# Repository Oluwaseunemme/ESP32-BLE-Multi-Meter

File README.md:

# ⚡ ESP32 BLE Multi-Meter

A custom **ESP32-based digital multimeter** capable of measuring **DC voltage, resistance, continuity, diode forward voltage, and capacitance**, with measurement results transmitted wirelessly to a **Flutter mobile application over Bluetooth Low Energy (BLE)**.

The project combines embedded firmware, analog measurement circuits, OLED display control, BLE communication, Flutter application development, KiCad PCB design, Proteus simulation, and object-oriented C++ firmware architecture.

---

## 📌 Project Overview

This project started as a collection of individual measurement experiments and evolved into a single multifunctional ESP32-based meter.

The meter can:

* Measure DC voltage
* Measure resistance
* Perform continuity testing
* Measure diode forward voltage
* Measure capacitance
* Display measurements locally on a **128×64 OLED**
* Send measurement results to a Flutter mobile application through **BLE**
* Provide a built-in resistor color-code calculator
* Calculate resistor series and parallel combinations
* Calculate capacitor series and parallel combinations
* Switch between measurement modes from the mobile application

The repository also contains the development stages of the project, including individual measurement programs, simulations, circuit designs, PCB layouts, and the final object-oriented firmware.

---

# 🧩 System Architecture

```text
                    ┌──────────────────────┐
                    │      Test Leads      │
                    └──────────┬───────────┘
                               │
                               ▼
                    ┌──────────────────────┐
                    │ Measurement Circuits │
                    │                      │
                    │ • Voltage            │
                    │ • Resistance          │
                    │ • Continuity         │
                    │ • Diode              │
                    │ • Capacitance        │
                    └──────────┬───────────┘
                               │
                               ▼
                    ┌──────────────────────┐
                    │        ESP32         │
                    │                      │
                    │ • ADC measurement    │
                    │ • Mode control       │
                    │ • Calculations       │
                    │ • OLED interface     │
                    │ • BLE communication  │
                    └───────┬───────┬──────┘
                            │       │
                     ┌──────▼───┐   │
                     │  OLED    │   │ BLE
                     │ 128×64   │   │
                     └──────────┘   │
                                    ▼
                          ┌──────────────────┐
                          │ Flutter Mobile   │
                          │      App         │
                          │                  │
                          │ • Live readings  │
                          │ • Calculators    │
                          │ • BLE interface  │
                          └──────────────────┘
```

---

# 🔧 Measurement Functions

## 1. Voltage Measurement

The ESP32 ADC is used to measure the scaled input voltage.

A resistor-divider network reduces the measured voltage to a level suitable for the ESP32 ADC, after which the firmware reconstructs the original voltage.

```text
Input Voltage
      │
      ▼
Resistor Divider
      │
      ▼
    ESP32 ADC
      │
      ▼
Voltage Calculation
      │
      ▼
OLED / BLE / Flutter
```

---

## 2. Resistance Measurement

Resistance is determined using a known reference resistor and the voltage developed across the unknown resistor.

Using the voltage-divider relationship:

$$
R_x = \frac{R_{ref}V_x}{V_{in}-V_x}
$$

The firmware converts the ADC measurement into resistance and automatically formats the result into an appropriate unit.

Example:

```text
35.30 Ω
497.47 Ω
12.00 kΩ
```

---

## 3. Continuity Testing

The continuity mode checks whether the resistance between the probes is below a defined threshold.

When continuity is detected, the meter can provide an audible indication through a buzzer while also displaying the result locally.

This makes the resistance measurement hardware usable as a dedicated continuity tester.

---

## 4. Diode Testing

The diode mode applies a controlled test condition to the diode and measures its forward voltage.

The measured voltage is then displayed as the diode's approximate forward voltage:

```text
Forward Voltage
      │
      ▼
   ESP32 ADC
      │
      ▼
Voltage Conversion
      │
      ▼
 OLED / Flutter
```

---

# 5. Capacitance Measurement

Capacitance is measured using the **RC charging time** of the capacitor under test.

For an RC circuit:

$$
V_C(t)=V_{CC}(1-e^{-t/RC})
$$

At approximately **63.2%** of the charging voltage:

$$
t=RC
$$

Therefore:

$$
\boxed{C=\frac{t}{R}}
$$

The firmware measures how long the capacitor takes to reach the 63.2% threshold and calculates its capacitance.

### Automatic Range Selection

Multiple charging resistors are used to accommodate different capacitor values.

```text
1 MΩ
100 kΩ
10 kΩ
1 kΩ
```

The firmware can select an appropriate resistor depending on the charging time, preventing large capacitors from requiring unnecessarily long measurements.

A transistor-controlled discharge path is also used to reset the capacitor before another measurement.

---

# 📱 Flutter BLE Application

The meter communicates with the mobile application using **Bluetooth Low Energy**.

The Flutter application provides:

### Live Measurement

Measurement values received from the ESP32 can be displayed on the phone.

```text
ESP32
  │
  │ BLE
  ▼
Flutter BLE Manager
  │
  ▼
Mobile UI
```

This allows the meter to function as both a standalone instrument and a wireless measurement device.

### Built-in Calculator

The application also contains several electronics calculators.

#### Resistor Color Code

The user can select resistor color bands and calculate the corresponding resistance and tolerance.

#### Resistor Series / Parallel

The application calculates equivalent resistance for:

* Series connections
* Parallel connections

#### Capacitor Series / Parallel

Equivalent capacitance can also be calculated for series and parallel capacitor configurations.

This makes the application useful not only for displaying measurements but also as a small electronics utility tool.

---

# 🖥️ Local OLED Interface

The meter uses a **128×64 OLED display** for local operation.

The OLED provides:

* Measurement values
* Measurement mode
* Meter status
* Local user feedback

The OLED allows the ESP32 meter to remain fully functional even when the phone is not connected.

---

# 🧠 Firmware Architecture

The project was developed progressively.

Individual measurement modes were first implemented and tested separately before being combined into the final meter firmware.

The repository therefore contains both:

### Individual Implementations

Separate firmware experiments for:

```text
Voltage
Resistance
Continuity
Diode
Capacitance
```

This made it easier to develop and debug each measurement system independently.

### Object-Oriented Implementation

The final firmware was reorganized into a more structured C++/OOP architecture.

The `meter_OOP` section contains the combined implementation where measurement operations are organized into reusable functions/classes rather than keeping every mode as an isolated program.

This also made it easier to integrate the measurement modes with the OLED interface and BLE communication.

---

# 🔌 Hardware Design

The hardware development went through schematic, simulation, breadboard, and PCB stages.

### KiCad

The repository contains the complete KiCad design files for the meter, including:

* Schematic
* PCB layout
* Component placement
* Routing
* PCB visualization / 3D representation

The PCB integrates the ESP32, measurement circuitry, display interface, power/control circuitry, and probe connections.

### Proteus

Proteus simulations were used during development to test individual measurement circuits and verify their behavior before hardware implementation.

---

# 🧪 Development Workflow

The project followed roughly this development process:

```text
Circuit Concept
      │
      ▼
Individual Arduino/ESP32 Test
      │
      ▼
Proteus Simulation
      │
      ▼
Breadboard Prototype
      │
      ▼
Measurement Verification
      │
      ▼
KiCad Schematic
      │
      ▼
PCB Design
      │
      ▼
ESP32 Firmware Integration
      │
      ▼
BLE Communication
      │
      ▼
Flutter Application
      │
      ▼
Final Multi-Meter
```

This repository therefore contains both the **final implementation and the development process behind it**.

---

# 📂 Repository Structure

```text
ESP32-Multi-Meter/
│
├── BLE_stuffs/
│   └── BLE experiments and communication code
│
├── displayInfo/
│   └── OLED/display-related experiments
│
├── get_capacitance_practice/
│   └── Early capacitance measurement experiments
│
├── getCap/
│   └── Capacitance measurement implementation
│
├── getCap_general/
│   └── General/extended capacitance implementation
│
├── getCap_schematic_simulation/
│   └── Capacitance circuit simulation/design
│
├── getDiode/
│   └── Diode measurement code
│
├── getOhm/
│   └── Resistance/continuity measurement
│
├── getVoltage/
│   └── Voltage measurement code
│
├── kicad_sch_pcb/
│   └── Complete KiCad schematic and PCB files
│
├── meter_OOP/
│   └── Combined object-oriented meter firmware
│
├── pcb_sch_img/
│   └── PCB and schematic images
│
└── Flutter_stuffs/
    └── Flutter mobile application
```

---

# 🛠️ Main Technologies

### Hardware

* ESP32
* 128×64 OLED
* ADC measurement circuits
* Resistor-divider networks
* Reference resistors
* Capacitor charging/discharging circuit
* Transistor-controlled discharge
* Buzzer
* Test probes

### Firmware

* C++
* Arduino framework
* ESP32 ADC
* GPIO
* Timers
* I²C
* Bluetooth Low Energy
* Object-Oriented Programming

### Software

* Flutter
* Dart
* KiCad
* Proteus
* Arduino IDE

---

# 📸 Project

The repository includes development and hardware documentation such as:

* KiCad schematic
* PCB layout
* PCB 3D visualization
* Proteus simulations
* Breadboard prototype
* ESP32 firmware
* Individual measurement implementations
* Combined OOP firmware
* Flutter application screenshots
* BLE development experiments

---

# 🎯 What This Project Demonstrates

This project brings together several areas of electronics and software engineering:

* Analog measurement
* ADC signal processing
* Voltage-divider calculations
* RC transient analysis
* Automatic measurement ranging
* Embedded C++
* Object-oriented firmware design
* OLED interfacing
* BLE communication
* Flutter application development
* PCB design
* Circuit simulation
* Hardware prototyping
* Embedded-to-mobile communication

Rather than relying on a single integrated multimeter IC, the project explores how common electronic measurement techniques can be implemented directly using a microcontroller and custom analog circuitry.

---

# 🚀 Future Improvements

Possible future improvements include:

* [ ] Improved measurement accuracy and calibration
* [ ] AC voltage measurement
* [ ] Current measurement
* [ ] Inductance measurement
* [ ] Capacitor ESR measurement
* [ ] Better input protection
* [ ] More measurement ranges
* [ ] Improved PCB enclosure
* [ ] Data logging and measurement history
* [ ] Exporting measurements from the Flutter application
* [ ] Rechargeable battery/power management
* [ ] Improved BLE reliability and connection handling

---

# 📜 License

This project is intended primarily for educational, experimental, and personal development purposes.

Feel free to explore, modify, and build upon the project.

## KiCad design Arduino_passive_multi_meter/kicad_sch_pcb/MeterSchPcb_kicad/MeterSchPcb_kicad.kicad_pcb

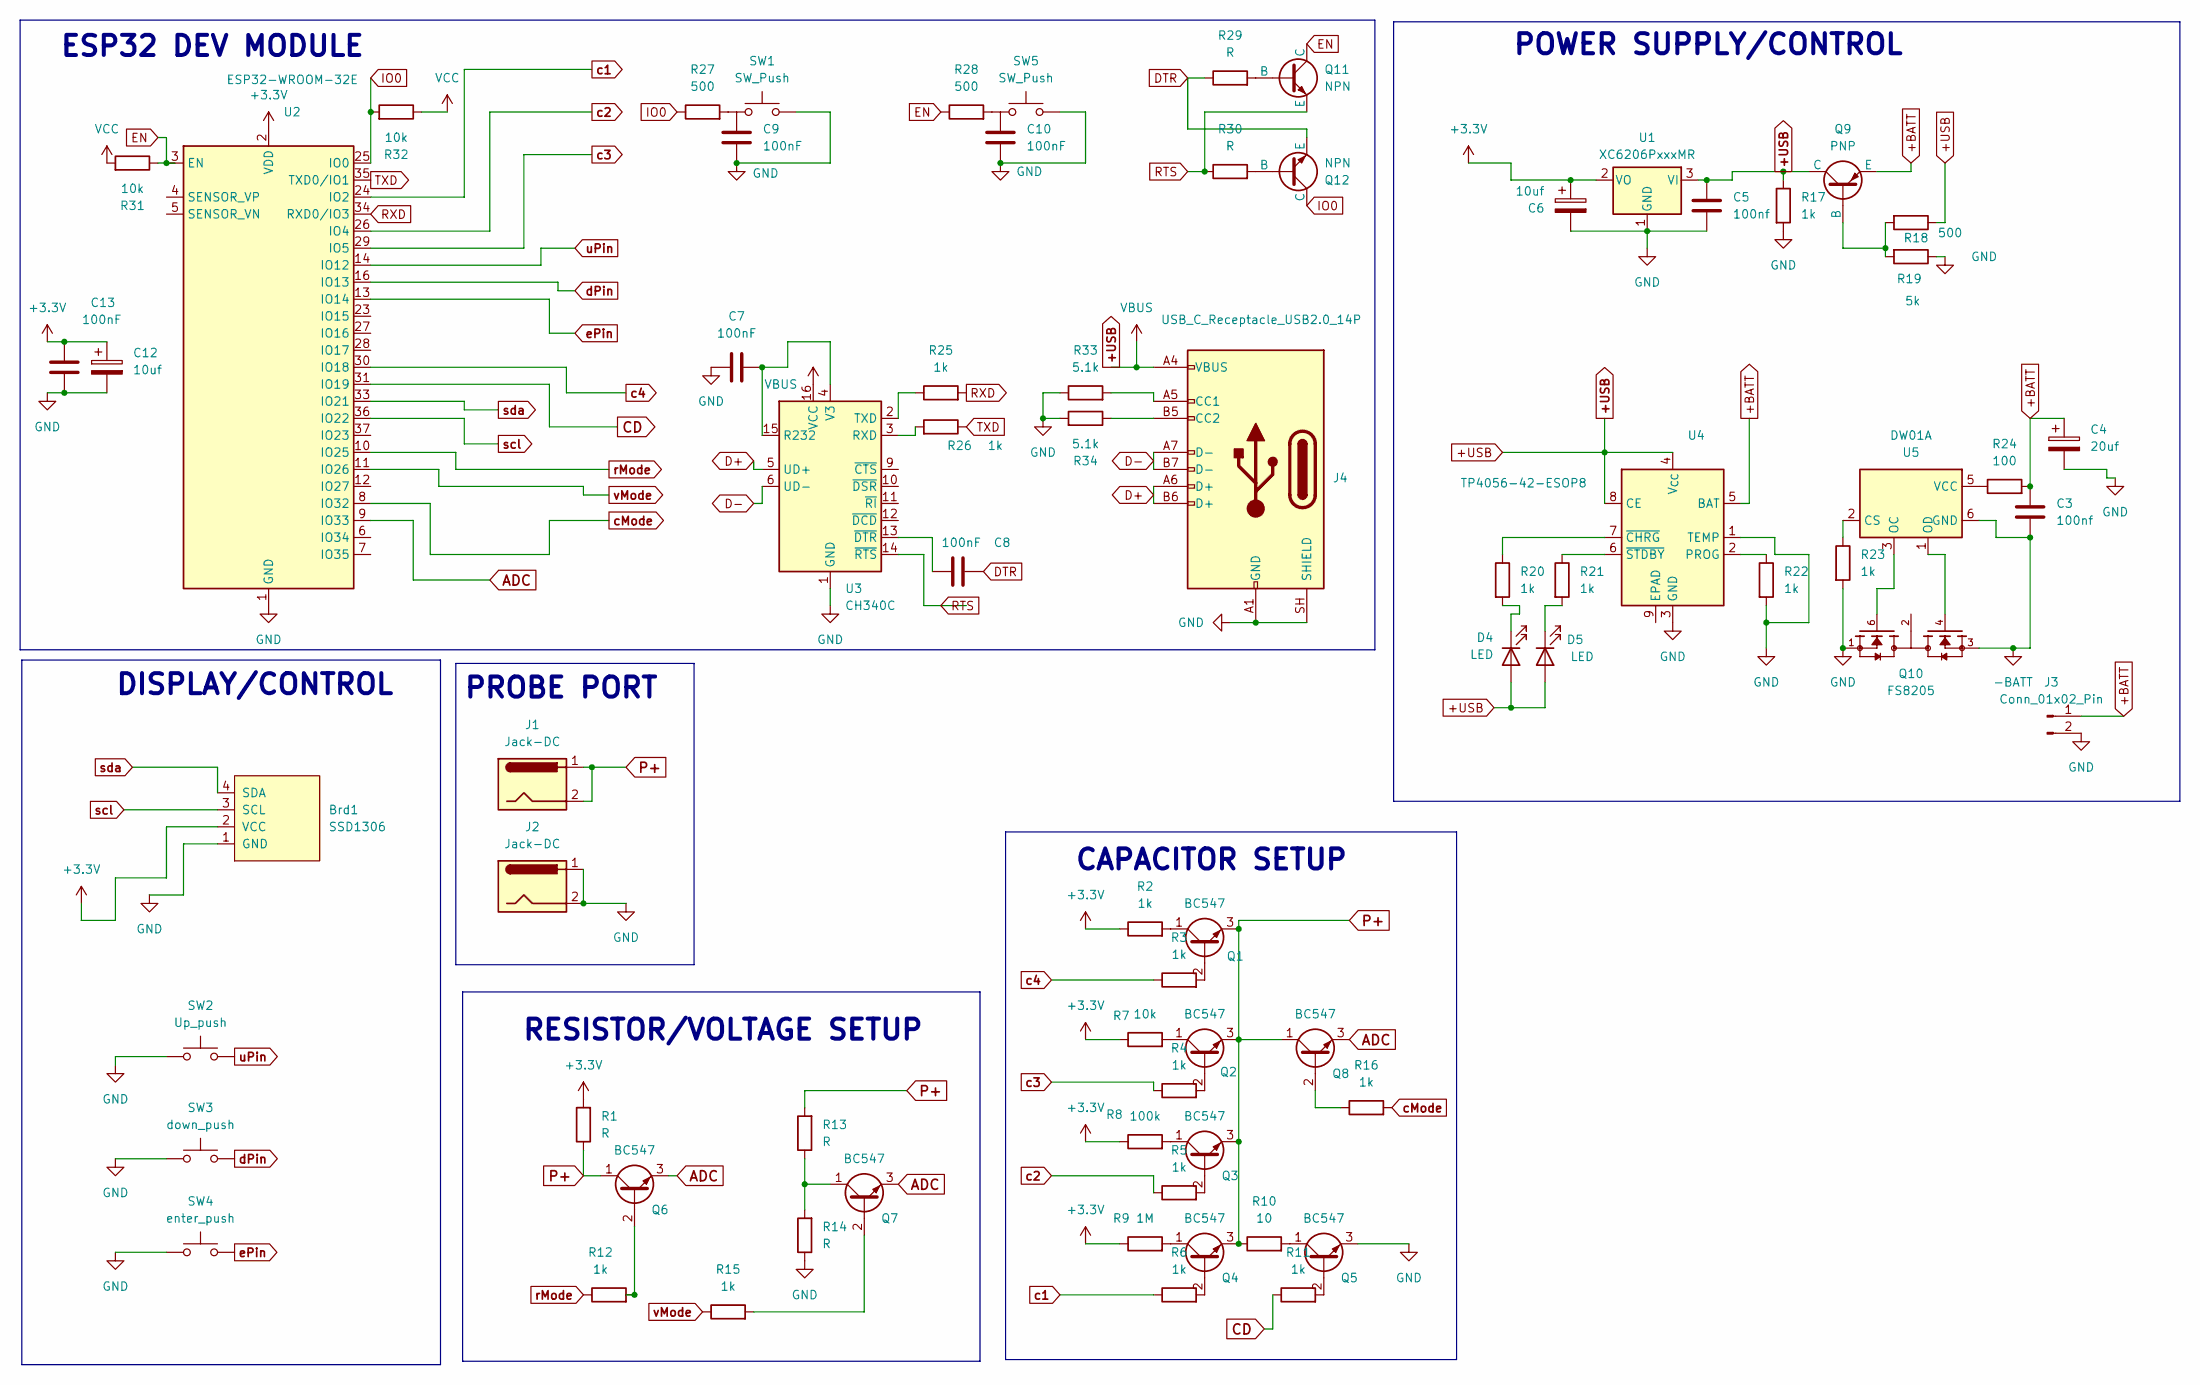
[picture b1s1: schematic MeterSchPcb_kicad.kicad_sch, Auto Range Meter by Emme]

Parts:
Brd1: SSD1306; 128x64OLED
C3, C5: 100nf; C_0603_1608Metric
C4: 20uf; CP_EIA-1608-08_AVX-J
C6, C12: 10uf; CP_EIA-1608-08_AVX-J
C7, C8, C9, C10, C13: 100nF; C_0603_1608Metric
D4, D5: LED; LED_0603_1608Metric_Pad1.05x0.95mm_HandSolder
J1, J2: Jack-DC; PinHeader_1x01_P2.54mm_Vertical
J3: Conn_01x02_Pin; PinHeader_1x02_P2.00mm_Vertical
J4: USB_C_Receptacle_USB2.0_14P; USB_C_Receptacle_GCT_USB4105-xx-A_16P_TopMnt_Horizontal
Q1, Q2, Q3, Q4, Q5, Q6, Q7, Q8: BC547; SOT-23
Q9: PNP; SOT-23-3
Q10: FS8205; SO-8_3.9x4.9mm_P1.27mm
Q11, Q12: NPN; SOT-23
R1, R13, R14, R29, R30: R; R_0603_1608Metric
R2, R3, R4, R5, R6, R11, R12, R15, R16, R25, R26: 1k; R_0603_1608Metric
R7, R31, R32: 10k; R_0603_1608Metric
R8: 100k; R_0603_1608Metric
R9: 1M; R_0603_1608Metric
R10: 10; R_0603_1608Metric
R17, R20, R21, R22, R23: 1k; R_0603_1608Metric_Pad0.98x0.95mm_HandSolder
R18: 500; R_0603_1608Metric_Pad0.98x0.95mm_HandSolder
R19: 5k; R_0603_1608Metric_Pad0.98x0.95mm_HandSolder
R24: 100; R_0603_1608Metric_Pad0.98x0.95mm_HandSolder
R27, R28: 500; R_0603_1608Metric
R33, R34: 5.1k; R_0603_1608Metric
SW1, SW5: SW_Push; SW_Push_1P1T_NO_CK_KMR2
SW2: Up_push; SW_Push_1P1T_NO_CK_KMR2
SW3: down_push; SW_Push_1P1T_NO_CK_KMR2
SW4: enter_push; SW_Push_1P1T_NO_CK_KMR2
U1: XC6206PxxxMR; SOT-23-3
U2: ESP32-WROOM-32E; ESP32-WROOM-32D
U3: CH340C; SOIC-16_3.9x9.9mm_P1.27mm
U4: TP4056-42-ESOP8; SOIC-8-1EP_3.9x4.9mm_P1.27mm_EP2.41x3.3mm_ThermalVias
U5: DW01A; SOT-23-6

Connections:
+3.3V: Brd1.2 (VCC), C6.1, C12.1, C13.1, R1.2, R2.1, R7.1, R8.1, R9.1, U1.2 (VO), U2.2 (VDD)
+BATT: C3.1, C4.1, J3.1, Q9.3 (E), R24.2, U4.5 (BAT)
+USB: C5.1, D4.2 (A), D5.2 (A), J4.A4 (VBUS), J4.A9 (VBUS), J4.B4 (VBUS), J4.B9 (VBUS), Q9.1 (C), R17.1, R18.1, U1.3 (VI), U3.16 (VCC), U4.4 (V_{CC}), U4.8 (CE)
-BATT: C3.2, Q10.3, U5.6 (GND)
ADC: Q6.3 (E), Q7.3 (E), Q8.3 (E), U2.9 (IO33)
CD: R11.1, U2.31 (IO19)
D+: J4.A6 (D+), J4.B6 (D+), U3.5 (UD+)
D-: J4.A7 (D-), J4.B7 (D-), U3.6 (UD-)
DTR: C8.2, Q12.3 (E), R29.1
EN: Q11.1 (C), R28.1, R31.1, U2.3 (EN)
GND: Brd1.1 (GND), C4.2, C5.2, C6.2, C7.1, C9.2, C10.2, C12.2, C13.2, J2.1, J2.2, J3.2, J4.A1 (GND), J4.A12 (GND), J4.B1 (GND), J4.B12 (GND), J4.SH (SHIELD), Q5.3 (E), Q10.1, R14.1, R17.2, R19.1, R22.2, R23.2, R33.1, R34.2, SW1.2, SW2.1, SW3.1, SW4.1, SW5.2, U1.1 (GND), U2.1 (GND), U2.15 (GND), U2.38 (GND), U2.39 (GND), U3.1 (GND), U4.1 (TEMP), U4.3 (GND)
IO0: Q12.1 (C), R27.1, R32.2, U2.25 (IO0)
unnamed: D4.1 (K), R20.2
unnamed: D5.1 (K), R21.2
unnamed: J4.A5 (CC1), R33.2
unnamed: J4.B5 (CC2), R34.1
unnamed: Q1.2 (B), R3.2
unnamed: Q1.1 (C), R2.2
unnamed: Q2.2 (B), R4.2
unnamed: Q2.1 (C), R7.2
unnamed: Q3.2 (B), R5.2
unnamed: Q3.1 (C), R8.2
unnamed: Q4.2 (B), R6.2
unnamed: Q4.1 (C), R9.2
unnamed: Q5.2 (B), R11.2
unnamed: Q5.1 (C), R10.2
unnamed: Q6.2 (B), R12.2
unnamed: Q7.2 (B), R15.2
unnamed: Q7.1 (C), R13.1, R14.2
unnamed: Q8.2 (B), R16.1
unnamed: Q9.2 (B), R18.2, R19.2
unnamed: Q10.2, Q10.5
unnamed: Q11.2 (B), R29.2
unnamed: Q12.2 (B), R30.2
unnamed: R27.2, SW1.1
unnamed: R28.2, SW5.1
unnamed: C7.2, U3.4 (V3), U3.15 (R232)
unnamed: R26.2, U3.3 (RXD)
unnamed: R25.1, U3.2 (TXD)
unnamed: C8.1, U3.13 (~DTR)
unnamed: R22.1, U4.2 (PROG)
unnamed: R20.1, U4.7 (~CHRG)
unnamed: R21.1, U4.6 (~STDBY)
unnamed: R23.1, U5.2 (CS)
unnamed: Q10.6, U5.3 (OC)
unnamed: Q10.4, U5.1 (OD)
unnamed: R24.1, U5.5 (VCC)
P+: J1.1, J1.2, Q1.3 (E), Q2.3 (E), Q3.3 (E), Q4.3 (E), Q6.1 (C), Q8.1 (C), R1.1, R10.1, R13.2
RTS: Q11.3 (E), R30.1, U3.14 (~RTS)
RXD: R25.2, U2.34 (RXD0/IO3)
TXD: R26.1, U2.35 (TXD0/IO1)
VCC: R31.2, R32.1
c1: R6.1, U2.24 (IO2)
c2: R5.1, U2.26 (IO4)
c3: R4.1, U2.29 (IO5)
c4: R3.1, U2.30 (IO18)
cMode: R16.2, U2.8 (IO32)
dPin: SW3.2, U2.16 (IO13)
ePin: SW4.2, U2.13 (IO14)
rMode: R12.1, U2.10 (IO25)
scl: Brd1.3 (SCL), U2.36 (IO22)
sda: Brd1.4 (SDA), U2.33 (IO21)
uPin: SW2.2, U2.14 (IO12)
vMode: R15.1, U2.11 (IO26)

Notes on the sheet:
PROBE PORT
RESISTOR/VOLTAGE SETUP
DISPLAY/CONTROL
POWER SUPPLY/CONTROL
CAPACITOR SETUP
ESP32 DEV MODULE

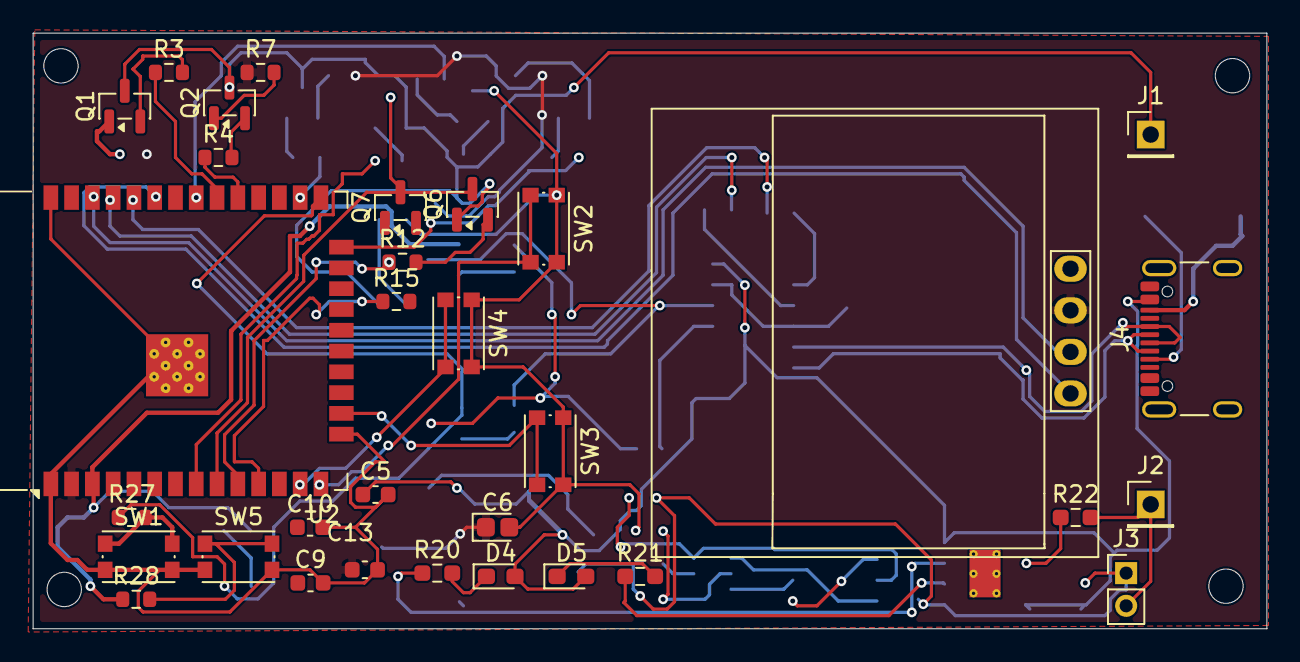
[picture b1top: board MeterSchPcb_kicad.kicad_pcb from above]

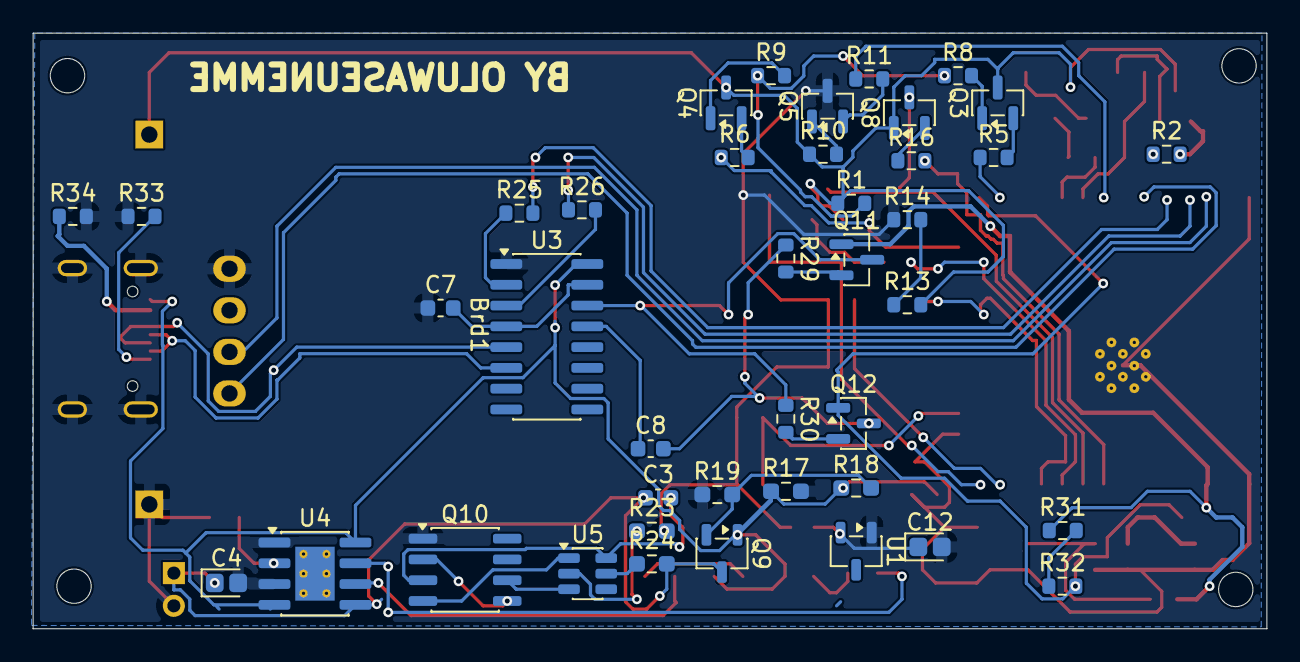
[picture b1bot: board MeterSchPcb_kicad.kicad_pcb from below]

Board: 2 copper layers, 75.4 x 36.4 mm, 73 parts (41 on the bottom side), 64 nets.
